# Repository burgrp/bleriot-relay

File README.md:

# BleRiot Relay

TinyGo/BleRiot firmware for the PY32F003/PAN2110 relay board, with one
active-low on/off triac output, an optional watchdog lease, and up to 20 externally
powered DS18B20 thermometers. No other sensor types are supported.

## Hardware

The firmware targets `py32f003x6`: 32 KiB flash, 4 KiB RAM, and a 24 MHz
CPU clock. The schematic uses the SOP16 `PY32F003W1xSx` pinout; verify that
the fitted part has at least this memory density. The pinout and density
follow the PY32F003 Datasheet Rev1.7, Figure 3-10 and Table 1-3.

| Function | MCU pin | Schematic net |
| --- | --- | --- |
| Relay/optotriac, active low | PB1 | `~TRIAC` |
| WS2812 status LED | PB0 | `LED` |
| DS18B20 data | PA0 | `SENS` |
| PAN2110 SCK | PA2 | `RF_SCK` |
| PAN2110 bidirectional data | PA1 | `RF_DATA` |
| PAN2110 CSN, active low | PA4 | `~RF_CS` |

Unlike the SOP8 Sense board, this SOP16 board has a separate reset pin;
firmware does not rewrite the PB0/reset option byte.

Connect DS18B20s in parallel on `SENS1`:

| Pin | Connection |
| ---: | --- |
| 1 | GND |
| 2 | DQ |
| 3 | +5 V sensor supply |

R7 is a 4.7 kOhm pull-up from `SENS` to 3.3 V, on the MCU side of the
existing R6 270-ohm series resistor and BAT54S protection. Do not add a
5 V DQ pull-up. The firmware uses open-drain PA0 and a 1 MHz TIM3 counter;
it does not substitute the MCU's weak internal pull-up. Parasite power is
unsupported and reported as a sensor fault.

R7 is included in both the schematic and the updated PCB. Regenerate the
existing fabrication outputs before manufacturing this revision. Older boards
without R7 need the pull-up retrofitted before using DS18B20s.

## Registers

The development inventory explicitly enables the watchdog and exports three
registers:

| Registry name | Wire tag | Type | Access |
| --- | ---: | --- | --- |
| `relay.state` | 1 | bool | Read/write |
| `relay.watchdog` | 2 | int, seconds | Read/write |
| `relay.temperature` | 256 | float, degrees Celsius | Read-only |

`relay.state` reports the commanded output, not electrical load feedback.
Wire boolean values are normalized to 0 or 1. NULL relay writes and unknown
or read-only writes are ignored, matching CPG's boolean-output behavior;
write `false` explicitly to turn the relay off.

Temperature tags are permanently reserved as 256-275, matching Sense's
dedicated DS18B20 range. With multiple configured sensors, Registry names
are `relay.temperature.1`, `relay.temperature.2`, and so on. Temperatures
are transmitted as signed Q12.4 integers and converted to Celsius in the
hub without losing the 1/16-degree resolution.

The number of temperature registers is inventory configuration, not discovery
order or the number of currently connected sensors. An empty sensor list
exports only state plus the watchdog if enabled. With `WatchdogEnabled: false`,
the watchdog register is absent, including when sensors are enabled.
Tag 2 remains reserved and temperature tags never shift.
The development inventory's one-temperature-register configuration
continues to export a NULL temperature if no sensor is connected.
Tags must not be renumbered or reused.

## Watchdog, Offline State, And LED

The relay always starts off. Firmware preloads PB1 high before enabling its
output driver, avoiding an active-low startup pulse.

`WatchdogEnabled` is a boolean firmware configuration property and defaults to
`false`. Set it to `true` to export `watchdog` and enforce its lease. When
disabled or omitted, relay writes need no lease, tag 2 reads return NULL and
writes are ignored, and there is no watchdog-expired blue indication.
Startup-off and RF-loss safety remain active in both modes.

An enabled watchdog starts expired. Positive writes arm a lease, clamped to
60 seconds. Reads return the remaining whole seconds rounded up.
Zero, negative, and NULL watchdog
writes expire the lease immediately. While expired, relay SETs are acknowledged
but ignored. Expiry clears the retained relay command and drives PB1 high.
Re-arming alone never restores the old command; send a fresh relay SET.

The node starts RF-offline. The default five-second timeout without a valid
BleRiot packet forces the same relay-off state and clears the retained command,
matching REG6. The development inventory explicitly selects five seconds;
external inventories can override it with `Instance.OnlineTimeout`.
Reconnection does not restore the command. If enabled, a still-active watchdog lease
is retained across RF loss; renew it if necessary and send a fresh relay SET.
A radio initialization failure also leaves the output off and runs the
offline heartbeat.

| Status | LED |
| --- | --- |
| RF offline, regardless of watchdog | Orange-red `0xff3000`, 200 ms on / 800 ms off |
| Online, enabled watchdog expired | Pure blue `0x0000ff`, 200 ms on / 800 ms off |
| Online, watchdog disabled or armed, relay off | Steady amber `0xa05000` |
| Online, watchdog disabled or armed, relay on | Steady green `0x00ff10` |

The heartbeat comes from BleRiot's status phase. Colors match CPG, with
REG6's global brightness limit of 128/255. RF offline has priority over
watchdog expiry. Temperature faults do not change the output or its LED status.

## Firmware Configuration

Edit `relayConfig` in [`fw/cmd/dev/main.go`](fw/cmd/dev/main.go).
The same config is passed to `spec.TypeForConfig` and baked into the firmware,
keeping the hub register table and node layout consistent:

```go
var relayConfig = spec.Config{
    WatchdogEnabled: true,
    SampleIntervalMilliseconds: 1000,
    DS18B20Sensors: []spec.DS18B20Sensor{{}},
}
```

To disable the watchdog, set `WatchdogEnabled: false` or omit the property.
Rebuild/reflash the node and restart the hub after changing it so register
export and firmware enforcement stay consistent.

One zero ID automatically binds only when exactly one DS18B20 is discovered.
If more than one is found, automatic binding is deliberately refused and the
temperature remains NULL. Firmware prints copy-pasteable `[8]byte{...}` ROM IDs
over RTT at boot. For multidrop, put one `spec.DS18B20Sensor{ID: ...}` entry
per register into the slice, using those IDs in the desired register order.
Every multidrop ID must be explicit, unique, family 0x28, and CRC-valid.

To disable temperatures, use `DS18B20Sensors: nil`. Up to 20 entries are
supported. Rebuild/reflash the node and restart the hub after changing the list.
An external inventory can use `RegistryNames` to give tags meaningful
deployment-specific names without changing their wire identities.

Sampling defaults to 1000 ms; intervals below 800 ms are raised to 800 ms.
Firmware configures addressed sensors for volatile 12-bit resolution,
broadcasts one conversion, waits the full 800 ms while servicing RF and
watchdog/LED status, then reads at most one sensor per main-loop pass.
The interval is measured from conversion start, and a large sensor bank
stretches the cycle rather than producing a blocking catch-up batch.

ROM and scratchpad CRCs, sensor power, configuration, and temperature range
are checked by the shared 1-Wire driver. Failed sensors become NULL independently
and are retried. A missing or stuck-low bus invalidates all temperature samples;
faults are reported over RTT. A previously missing automatic single sensor
can bind when connected later. An ambiguous automatic bus requires explicit
IDs or a reboot after correcting the wiring.

## Build And Run

The importable firmware module and specification are in [`fw/`](fw/).
External inventories import:

```go
import "github.com/burgrp/bleriot-relay/fw/spec"
```

Dependencies are pinned in [`fw/go.mod`](fw/go.mod). Use Go 1.25.2 or newer,
TinyGo with `py32f003x6` support, GNU Arm Embedded binutils, and pyOCD with
the Puya PY32F003 pack. The build profile uses scheduler-none, a 1 KiB system
stack, leaking GC, and RTT serial.

Both watchdog modes with 0, 1, and 20 sensors were built with Go 1.26.3 and
TinyGo 0.42.0-dev-f8e1f465 / LLVM 18.1.8:

| Watchdog | Temperature registers | Flash, including initialized data | Reserved RAM |
| --- | ---: | ---: | ---: |
| Disabled | 0 | 15,644 bytes | 2,224 bytes |
| Disabled | 1, automatic | 16,508 bytes | 2,224 bytes |
| Disabled | 20, explicit IDs | 16,948 bytes | 2,224 bytes |
| Enabled | 0 | 15,652 bytes | 2,224 bytes |
| Enabled | 1, automatic | 16,512 bytes | 2,224 bytes |
| Enabled | 20, explicit IDs | 16,948 bytes | 2,224 bytes |

Reserved RAM includes the 1,024-byte system stack and static data, leaving
1,872 bytes for the heap. Host tests verify allocation-free steady-state
control and temperature sampling, and cover optional-watchdog behavior,
fail-safe, LED priority, discovery,
sensor isolation/recovery, timing, and the register/conversion contract.
The updated schematic/PCB pass ERC, DRC, and schematic parity checks.
Hardware has not been flashed or exercised as part of this implementation.

```sh
go -C fw test ./...
make -C fw build
go -C fw run ./cmd/dev node gen --name relay
make -C fw install-pack
make -C fw flash
```

The default ELF and size report are generated under
[`fw/.bleriot/firmware/relay/`](fw/.bleriot/firmware/relay/), not directly in
the firmware module directory.

The flash target programs the board and opens RTT. Confirm the intended
board and probe before using it. The SOP16 SWD pins are PA13 (DIO) and
PA14/PF1 (CLK); `X1` has no target-voltage or reset connection.

**The checked-in development inventory uses an intentionally public bench
address and all-zero XTEA key on RF channel 37 / S8. Do not deploy this identity.**
Use `make -C fw new` to generate private provisioning for your own inventory,
kept outside tracked source. Never commit production keys. External inventories
can import this specification and build their own baked identity.

With a Registry server and the matching MCP2210/PAN2110 hub dongle:

```sh
go -C fw run ./cmd/dev hub --registry http://localhost:8080 --diagnostics rf
```

When enabled, renew `relay.watchdog` before commanding `relay.state`. Temperature registers
are polled by the hub; measurements do not require an armed output watchdog.

## Bench Validation

Start with an isolated low-voltage supply and no mains connected:

1. Confirm PB1 stays high at power-up and the LED shows the offline heartbeat.
2. Start RF traffic, arm a short watchdog, and send fresh on/off commands.
   Confirm PB1 is low only for the on command and the LED is green/amber.
3. Stop watchdog renewals while maintaining RF traffic. Confirm PB1 goes
   high, state reads false, and the LED blinks blue. Re-arm without a relay
   SET and verify the output remains off.
4. Command on, stop RF traffic for five seconds, and confirm output off
   with the orange-red heartbeat. Restore RF without a relay SET and verify
   it remains off.
5. Verify R7 is fitted, test zero/one/multiple DS18B20s, and use explicit ROM
   IDs for multidrop. Check negative temperatures, unplug one sensor, and
   confirm its NULL does not invalidate neighboring sensors.
6. Repeat watchdog/RF-loss tests during conversion and addressed reads.
   Scope the 1-Wire waveform and test the actual cable/sensor population.
7. Rebuild with `WatchdogEnabled: false` and restart the hub. Verify watchdog
   is absent, relay SETs work without a lease, online status is steady amber/green,
   and RF loss still switches the output off with the orange-red heartbeat.

The triac output is on/off only, not a dimmer. Mains testing, load suitability,
protection, isolation, enclosure, and thermal checks require qualified personnel.
Firmware builds and host tests do not replace electrical or hardware-in-loop
validation.

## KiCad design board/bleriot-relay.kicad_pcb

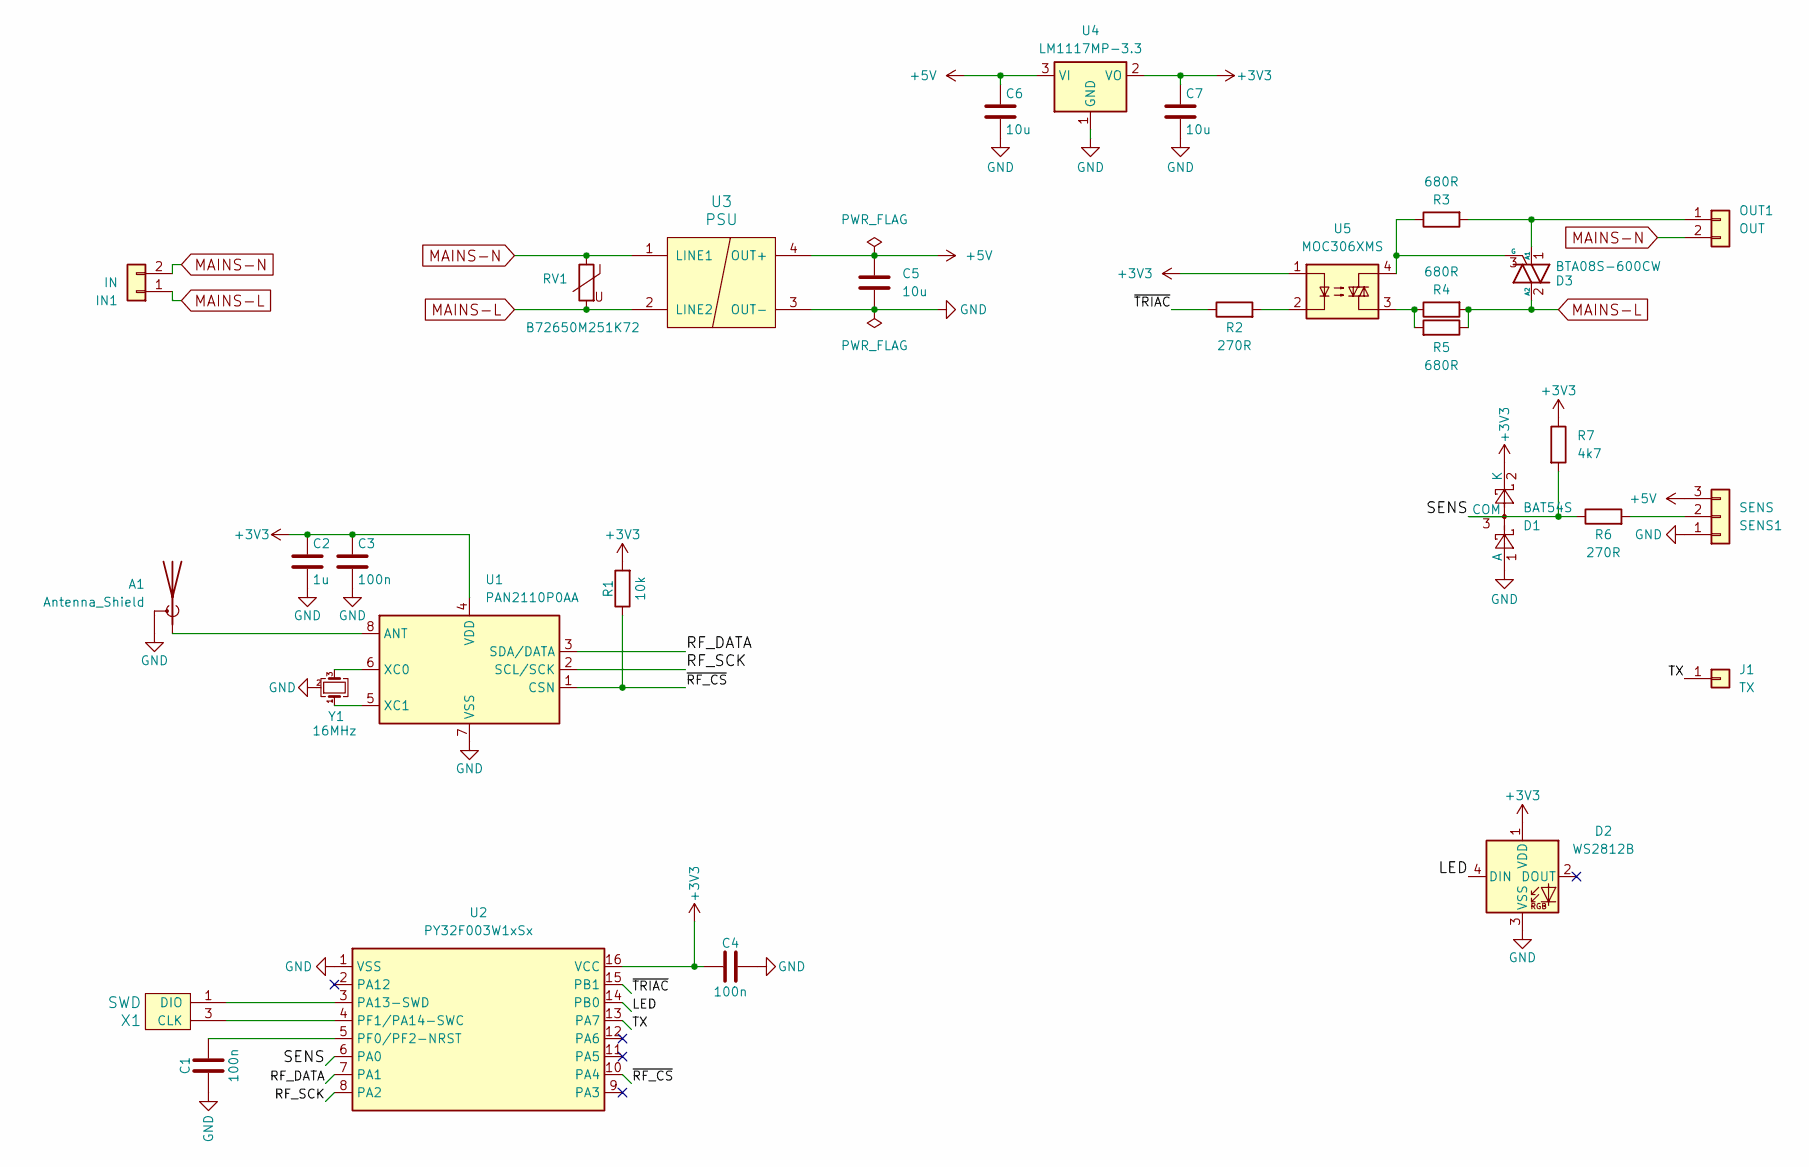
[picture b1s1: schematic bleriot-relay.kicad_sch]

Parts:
A1: Antenna_Shield; Texas_SWRA117D_2.4GHz_Right
C1, C3, C4: 100n; C_0805_2012Metric
C2: 1u; C_0805_2012Metric
C5, C6, C7: 10u; C_0805_2012Metric
D1: BAT54S; SOT-23
D2: WS2812B; LED_WS2812B_PLCC4_5.0x5.0mm_P3.2mm
D3: BTA08S-600CW; TO-252-2
IN1: IN; PhoenixContact_MSTBA_2,5_2-G_1x02_P5.00mm_Horizontal
J1: TX; PinHeader_1x01_P2.54mm_Vertical
OUT1: OUT; PhoenixContact_MSTBA_2,5_2-G_1x02_P5.00mm_Horizontal
R1: 10k; R_0805_2012Metric
R2, R6: 270R; R_0805_2012Metric
R3, R4, R5: 680R; R_0805_2012Metric
R7: 4k7; R_0805_2012Metric
RV1: B72650M251K72; R_1210_3225Metric
SENS1: SENS; PhoenixContact_MSTBA_2,5_3-G_1x03_P5.00mm_Horizontal
U1: PAN2110P0AA; SOIC-8_3.9x4.9mm_P1.27mm
U2: PY32F003W1xSx; SOIC-16_3.9x9.9mm_P1.27mm
U3: PSU; RQG 5V-0.6A-horizontal
U4: LM1117MP-3.3; SOT-223-3_TabPin2
U5: MOC306XMS; SMDIP-4_W7.62mm
X1: SWD
Y1: 16MHz; Crystal_SMD_3225-4Pin_3.2x2.5mm

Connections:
+3V3: C2.1, C3.1, C4.1, C7.1, D1.2 (K), D2.1 (VDD), R1.2, R7.1, U1.4 (VDD), U2.16 (VCC), U4.2 (VO), U5.1
+5V: C5.1, C6.1, SENS1.3, U3.4 (OUT+), U4.3 (VI)
/LED: D2.4 (DIN), U2.14 (PB0)
/RF_DATA: U1.3 (SDA/DATA), U2.7 (PA1)
/RF_SCK: U1.2 (SCL/SCK), U2.8 (PA2)
/SENS: D1.3 (COM), R6.1, R7.2, U2.6 (PA0)
/TX: J1.1 (Pin_1_1), U2.13 (PA7)
/~RF_CS: R1.1, U1.1 (CSN), U2.10 (PA4)
/~TRIAC: R2.1, U2.15 (PB1)
GND: A1.2 (Shield), C1.2, C2.2, C3.2, C4.2, C5.2, C6.2, C7.2, D1.1 (A), D2.3 (VSS), SENS1.1, U1.7 (VSS), U2.1 (VSS), U3.3 (OUT-), U4.1 (GND), X1.2 (GND), Y1.2 (G), Y1.4 (G)
MAINS-L: D3.2 (A2), IN1.1, R4.2, R5.1, RV1.2, U3.2 (LINE2)
MAINS-N: IN1.2, OUT1.2, RV1.1, U3.1 (LINE1)
unnamed: A1.1 (A), U1.8 (ANT)
unnamed: D3.1 (A1), OUT1.1, R3.2
unnamed: D3.3 (G), R3.1, U5.4
unnamed: R2.2, U5.2
unnamed: R4.1, R5.2, U5.3
unnamed: R6.2, SENS1.2
unnamed: U1.6 (XC0), Y1.3
unnamed: U1.5 (XC1), Y1.1
unnamed: U2.3 (PA13-SWD), X1.1 (DIO)
unnamed: C1.1, U2.5 (PF0/PF2-NRST)
unnamed: U2.4 (PF1/PA14-SWC), X1.3 (CLK)

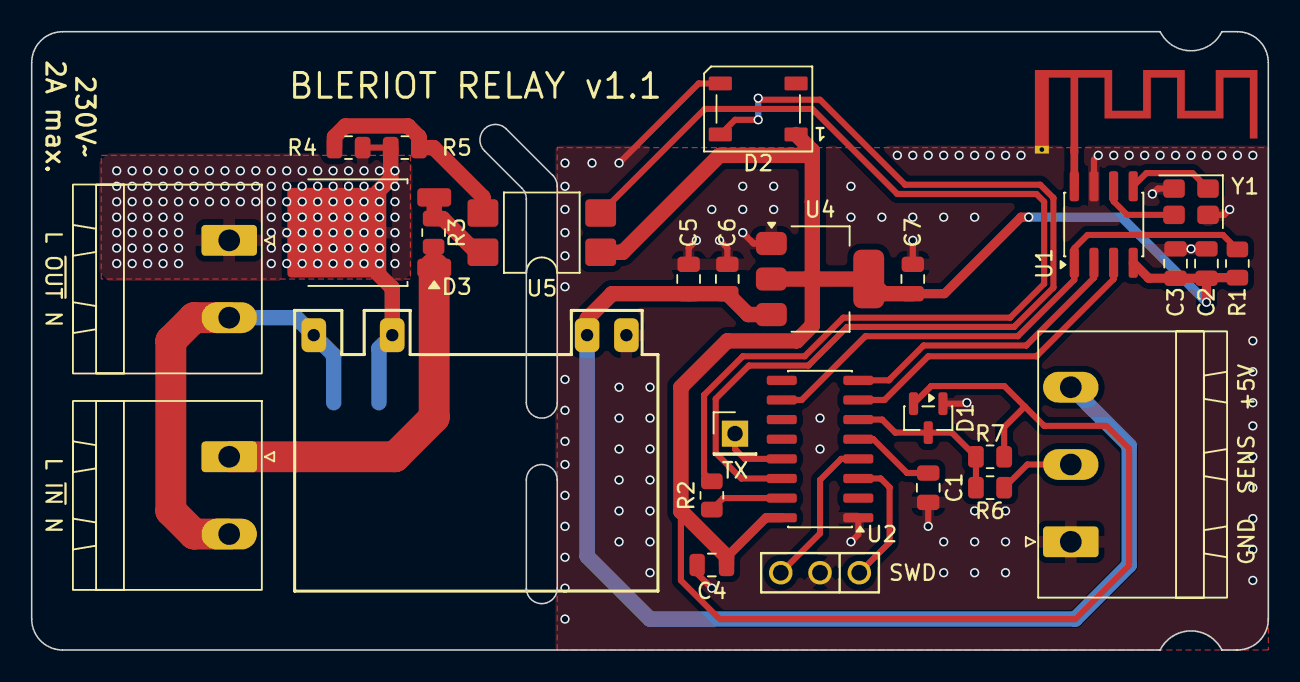
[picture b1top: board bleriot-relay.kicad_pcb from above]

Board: 2 copper layers, 80.0 x 40.0 mm, 30 parts (1 on the bottom side), 23 nets.
